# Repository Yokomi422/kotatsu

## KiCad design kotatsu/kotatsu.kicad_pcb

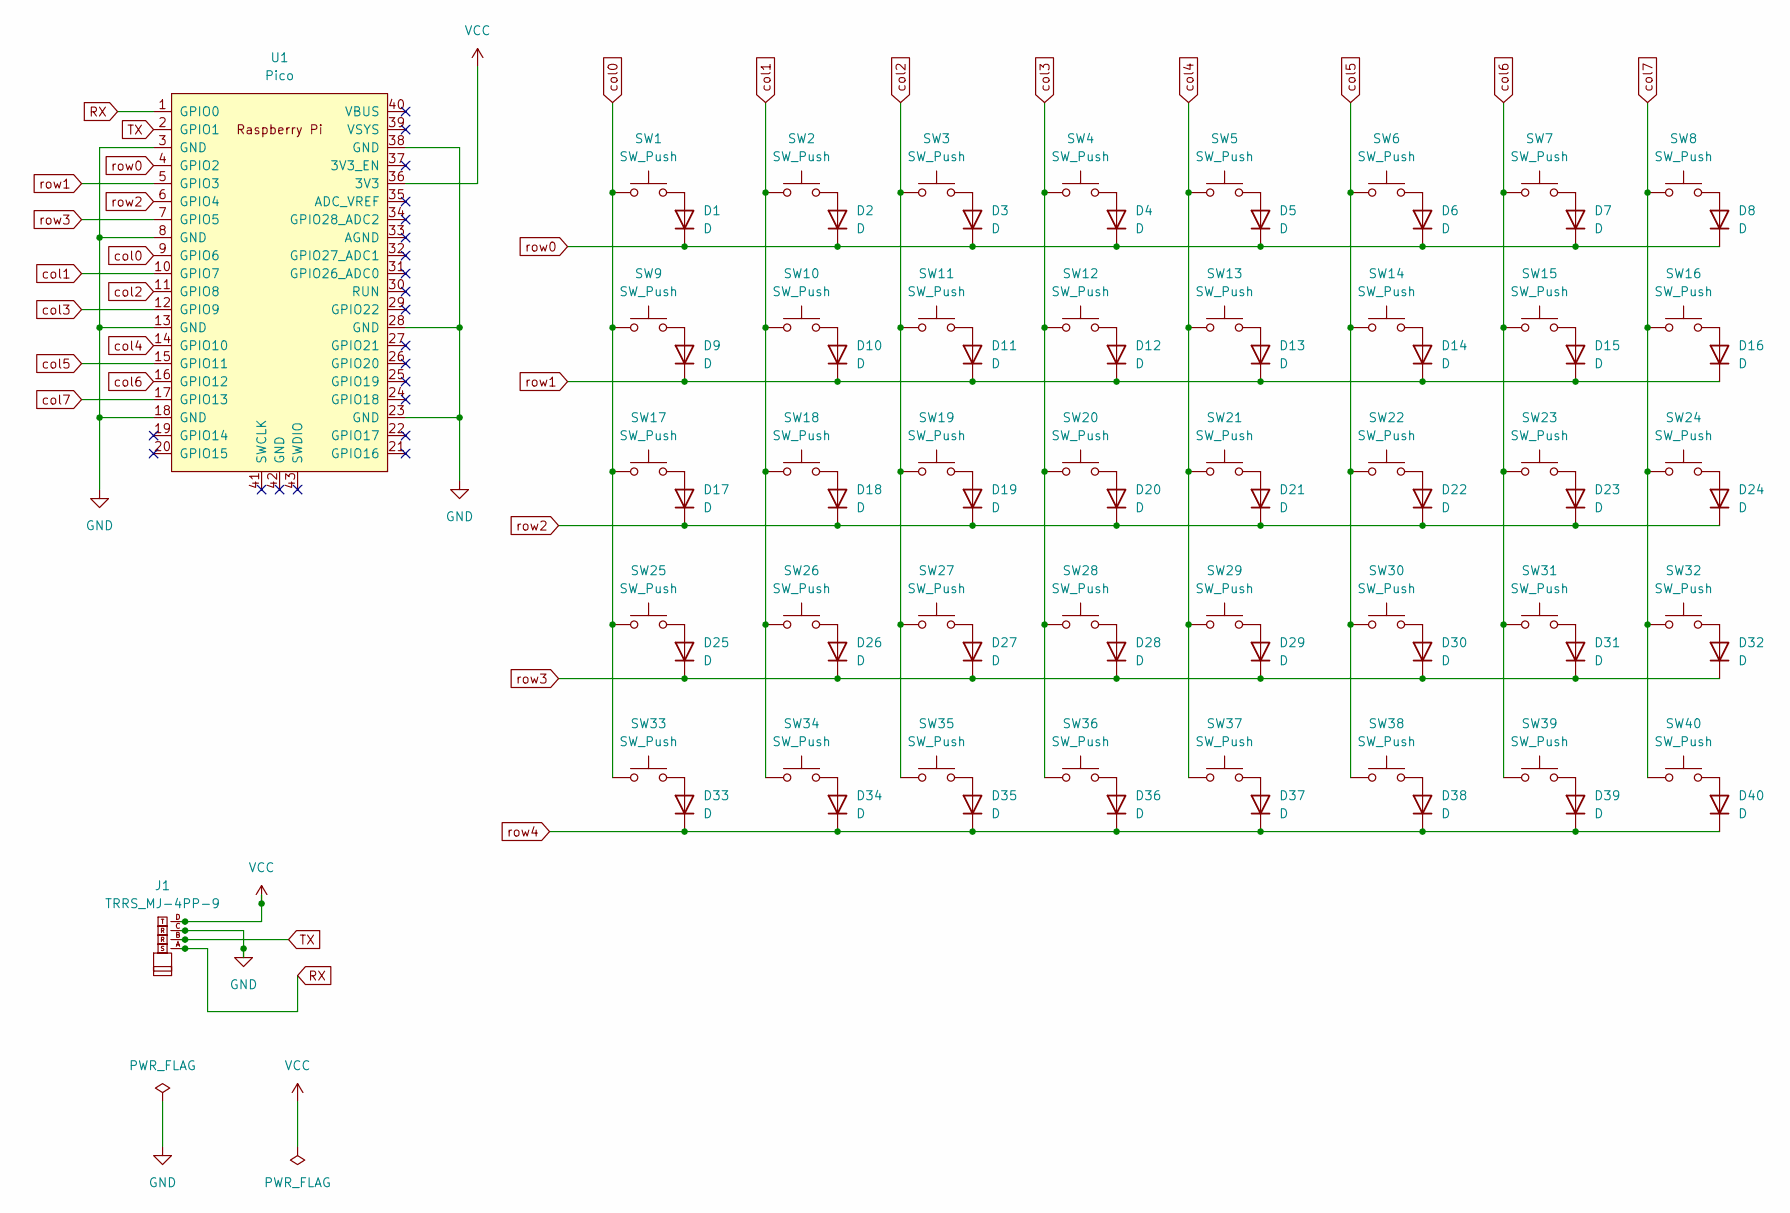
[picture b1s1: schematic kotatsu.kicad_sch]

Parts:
D1, D2, D3, D4, D5, D6, D7, D8, D9, D10, D11, D12, D13, D14, D15, D16, D17, D18, D19, D20, D21, D22, D23, D24, D25, D26, D27, D28, D29, D30, D31, D32, D33, D34, D35, D36, D37, D38, D39, D40: D; D_MELF-RM10_Universal_Handsoldering
J1: TRRS_MJ-4PP-9
SW1, SW9, SW17, SW25: SW_Push; SW_Cherry_MX_1.75u_PCB
SW2, SW3, SW4, SW5, SW6, SW7, SW8, SW10, SW11, SW12, SW13, SW14, SW15, SW16, SW18, SW19, SW20, SW21, SW22, SW23, SW24, SW26, SW27, SW28, SW29, SW30, SW31, SW33, SW34, SW35, SW37, SW38, SW39, SW40: SW_Push; SW_Cherry_MX_1.00u_PCB
SW32: SW_Push; SW_Cherry_MX_2.00u_Vertical_PCB
SW36: SW_Push; SW_Cherry_MX_2.00u_PCB
U1: Pico; RaspberryPi_Pico_SMD

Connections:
GND: J1.C, U1.3 (GND), U1.8 (GND), U1.13 (GND), U1.18 (GND), U1.23 (GND), U1.28 (GND), U1.38 (GND)
unnamed: D1.2 (A), SW1.2
unnamed: D2.2 (A), SW2.2
unnamed: D3.2 (A), SW3.2
unnamed: D4.2 (A), SW4.2
unnamed: D5.2 (A), SW5.2
unnamed: D6.2 (A), SW6.2
unnamed: D7.2 (A), SW7.2
unnamed: D8.2 (A), SW8.2
unnamed: D9.2 (A), SW9.2
unnamed: D10.2 (A), SW10.2
unnamed: D11.2 (A), SW11.2
unnamed: D12.2 (A), SW12.2
unnamed: D13.2 (A), SW13.2
unnamed: D14.2 (A), SW14.2
unnamed: D15.2 (A), SW15.2
unnamed: D16.2 (A), SW16.2
unnamed: D17.2 (A), SW17.2
unnamed: D18.2 (A), SW18.2
unnamed: D19.2 (A), SW19.2
unnamed: D20.2 (A), SW20.2
unnamed: D21.2 (A), SW21.2
unnamed: D22.2 (A), SW22.2
unnamed: D23.2 (A), SW23.2
unnamed: D24.2 (A), SW24.2
unnamed: D25.2 (A), SW25.2
unnamed: D26.2 (A), SW26.2
unnamed: D27.2 (A), SW27.2
unnamed: D28.2 (A), SW28.2
unnamed: D29.2 (A), SW29.2
unnamed: D30.2 (A), SW30.2
unnamed: D31.2 (A), SW31.2
unnamed: D32.2 (A), SW32.2
unnamed: D33.2 (A), SW33.2
unnamed: D34.2 (A), SW34.2
unnamed: D35.2 (A), SW35.2
unnamed: D36.2 (A), SW36.2
unnamed: D37.2 (A), SW37.2
unnamed: D38.2 (A), SW38.2
unnamed: D39.2 (A), SW39.2
unnamed: D40.2 (A), SW40.2
RX: J1.A, U1.1 (GPIO0)
TX: J1.B, U1.2 (GPIO1)
VCC: J1.D, U1.36 (3V3)
col0: SW1.1, SW9.1, SW17.1, SW25.1, SW33.1, U1.9 (GPIO6)
col1: SW2.1, SW10.1, SW18.1, SW26.1, SW34.1, U1.10 (GPIO7)
col2: SW3.1, SW11.1, SW19.1, SW27.1, SW35.1, U1.11 (GPIO8)
col3: SW4.1, SW12.1, SW20.1, SW28.1, SW36.1, U1.12 (GPIO9)
col4: SW5.1, SW13.1, SW21.1, SW29.1, SW37.1, U1.14 (GPIO10)
col5: SW6.1, SW14.1, SW22.1, SW30.1, SW38.1, U1.15 (GPIO11)
col6: SW7.1, SW15.1, SW23.1, SW31.1, SW39.1, U1.16 (GPIO12)
col7: SW8.1, SW16.1, SW24.1, SW32.1, SW40.1, U1.17 (GPIO13)
row0: D1.1 (K), D2.1 (K), D3.1 (K), D4.1 (K), D5.1 (K), D6.1 (K), D7.1 (K), D8.1 (K), U1.4 (GPIO2)
row1: D9.1 (K), D10.1 (K), D11.1 (K), D12.1 (K), D13.1 (K), D14.1 (K), D15.1 (K), D16.1 (K), U1.5 (GPIO3)
row2: D17.1 (K), D18.1 (K), D19.1 (K), D20.1 (K), D21.1 (K), D22.1 (K), D23.1 (K), D24.1 (K), U1.6 (GPIO4)
row3: D25.1 (K), D26.1 (K), D27.1 (K), D28.1 (K), D29.1 (K), D30.1 (K), D31.1 (K), D32.1 (K), U1.7 (GPIO5)
row4: D33.1 (K), D34.1 (K), D35.1 (K), D36.1 (K), D37.1 (K), D38.1 (K), D39.1 (K), D40.1 (K)

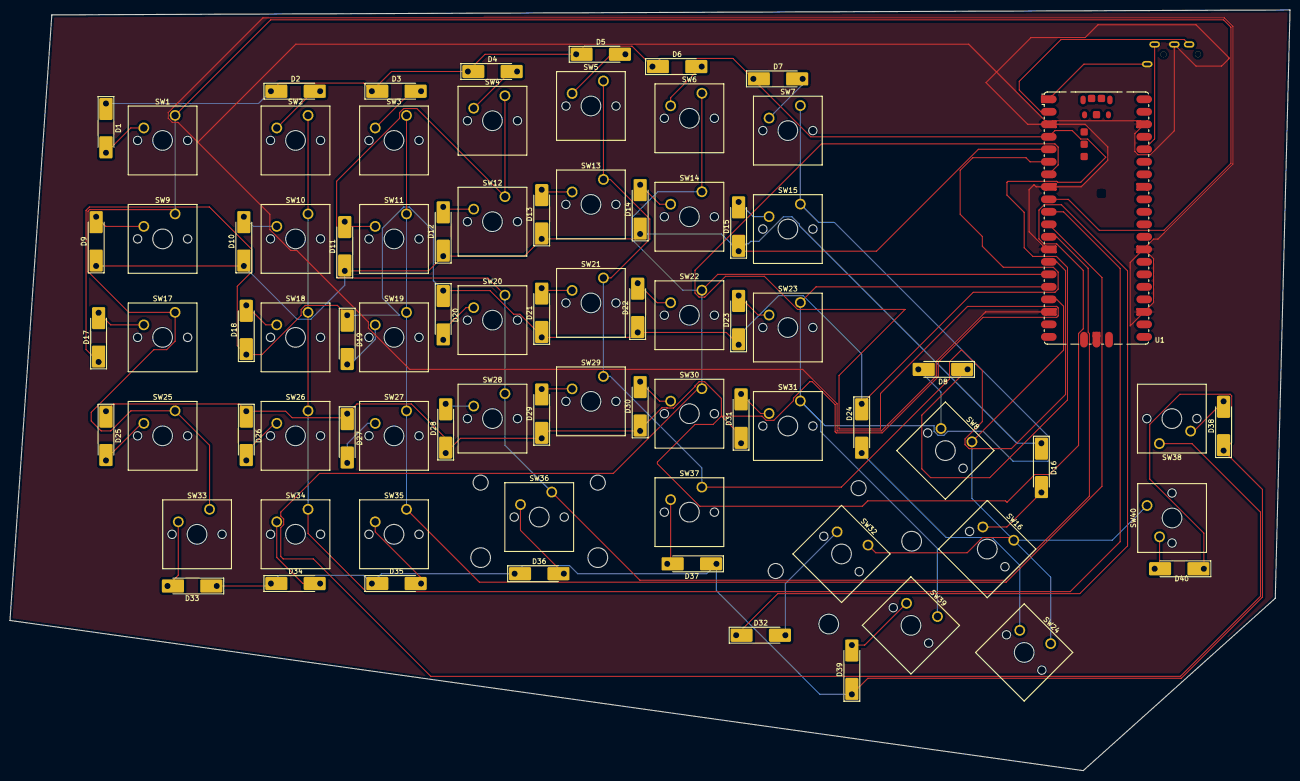
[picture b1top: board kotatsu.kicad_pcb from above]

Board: 2 copper layers, 260.0 x 154.5 mm, 82 parts (0 on the bottom side), 57 nets.

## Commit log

2025-03-08 put initial kicad files
2025-03-08 add pico and switches
2025-03-08 add labels
2025-03-08 add labels to pico
2025-03-11 回路図エディタ側の作業を完了した
2025-03-16 add json layout file
2025-03-19 annotated kotatsu
2025-03-20 Circuit editing completed
2025-03-20 RXTXマスター
2025-03-20 add kotatsu_right
2025-03-20 not clear what have been changed
2025-03-20 add image
2025-03-20 wiring ongoing
2025-03-20 right board completed
2025-03-20 bangyo
